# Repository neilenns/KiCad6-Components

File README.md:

# KiCad6 Custom Components

Custom components for use with KiCad 6.

## How to use

1. Clone the git repo.
2. Add a path in Kicad called `KICAD6_CUSTOM_COMPONENTS_DIR` that points to the locally cloned folder.
3. Add the `Custom_Symbols.kicad_sym` file as a custom symbol library.
4. Add the `Custom_Footprints.pretty` folder as a custom footprints library.

Here's an example of how the `Configure Paths` page should look;

Here's an example of how the `Symbols Libaries` page should look:

Here's an example of how the `Footprints Libraries` page should look:

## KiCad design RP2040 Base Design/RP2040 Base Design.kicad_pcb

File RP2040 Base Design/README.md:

# RP2040 Base PCB design

This KiCad template contains a base RP2040 schematic and PCB layout. To use this template go to _File_ > _New Project From Template..._,
switch to the _User Templates_ tab, then click the folder icon and navigate to this folder.

JLCPCB component numbers and footprints are included in the schematic as custom symbol properties.

**WARNING** While I've made a PCB using this design it was not done using this exact template. No boards have been ordered yet using this template so
if you use it and place an order while this message is still in place it is at your own risk.

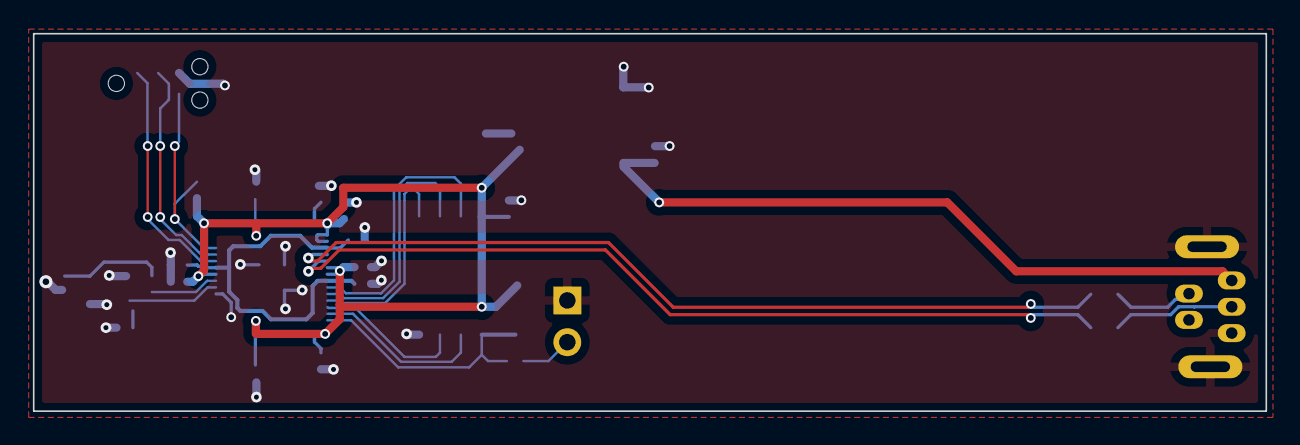
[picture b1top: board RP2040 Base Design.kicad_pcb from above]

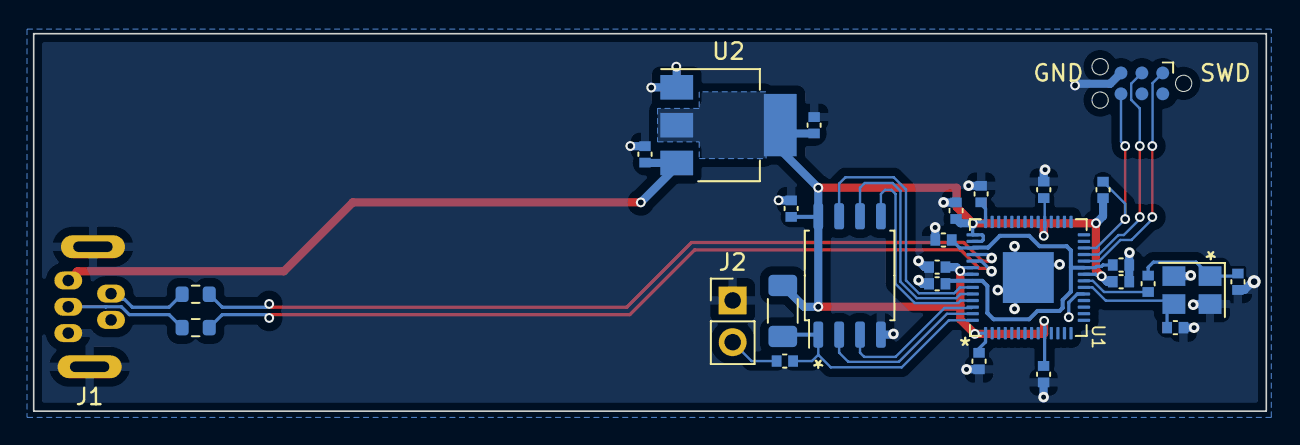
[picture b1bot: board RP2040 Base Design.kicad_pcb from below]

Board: 2 copper layers, 75.0 x 23.0 mm, 28 parts (28 on the bottom side), 21 nets.

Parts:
C1, C2, C3, C7, C10: 1uF; Perfect_0402
C4, C5: 10pF; Perfect_0402
C6, C8, C9, C11, C12, C13, C14, C15: 100nF; Perfect_0402
J1: USB_B_Micro; USB_B_Mini_Amphenol_UE25BE5510H
J2: Conn_01x02; PinHeader_1x02_P2.54mm_Vertical
J3: RP2040_SWD; Tag-Connect_TC2030-IDC-NL_2x03_P1.27mm_Vertical
R1, R2: 1k; Perfect_0402
R3, R4: 27; R_0603_1608Metric
R5: DNF; R_1206_3216Metric_Pad1.30x1.75mm_HandSolder
R6: 10k; Perfect_0402
U1: RP2040; QFN56P40_700X700X90L40X18T310N
U2: AMS1117-3.3; SOT-223-3_TabPin2
U3: W25Q128JVS; SOIC-8_5.23x5.23mm_P1.27mm
Y1: X322512MSB4SI; Crystal_SMD_3225-4Pin_3.2x2.5mm

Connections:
+1V1: C6.1, C7.1, C8.1, U1.23 (DVDD), U1.45 (VREG_VOUT), U1.50 (DVDD)
+3V3: C2.1, C3.1, C9.1, C10.1, C11.1, C12.1, C13.1, C14.1, C15.1, R5.1, R6.1, U1.1 (IOVDD), U1.10 (IOVDD), U1.22 (IOVDD), U1.33 (IOVDD), U1.42 (IOVDD), U1.43 (ADC_AVDD), U1.44 (VREG_IN), U1.48 (USB_VDD), U1.49 (IOVDD), U2.2 (VO), U3.8 (VCC)
+5V: C1.1, J1.1 (VBUS), U2.3 (VI)
/RP2040/QSPI_SCLK: U1.52 (QSPI_SCLK), U3.6 (CLK)
/RP2040/QSPI_SD0: U1.53 (QSPI_SD0), U3.5 (DI(IO0))
/RP2040/QSPI_SD1: U1.55 (QSPI_SD1), U3.2 (DO(IO1))
/RP2040/QSPI_SD2: U1.54 (QSPI_SD2), U3.3 (IO2)
/RP2040/QSPI_SD3: U1.51 (QSPI_SD3), U3.7 (IO3)
/RP2040/QSPI_SS: R1.1, R5.2, U1.56 (QSPI_SS), U3.1 (~CS)
/RP2040/SWCLK: J3.3, U1.25 (SWD)
/RP2040/SWD: J3.1, U1.24 (SWCLK)
/RP2040/USB_D+: J1.3 (D+), R3.1
/RP2040/USB_D-: J1.2 (D-), R4.1
/RP2040/USB_D_R+: R3.2, U1.47 (USB_DP)
/RP2040/USB_D_R-: R4.2, U1.46 (USB_DM)
/RP2040/XIN: C4.1, U1.20 (XIN), Y1.3
/RP2040/XOUT: C5.1, R2.2, Y1.1
/RP2040/XOUT_R: R2.1, U1.21 (XOUT)
/RP2040/~RST: J3.6, R6.2, U1.26 (RUN)
/RP2040/~USB_BOOT: J2.2, R1.2
GND: C1.2, C2.2, C3.2, C4.2, C5.2, C6.2, C7.2, C8.2, C9.2, C10.2, C11.2, C12.2, C13.2, C14.2, C15.2, J1.5 (GND), J1.6 (Shield), J2.1, J3.5, U1.19 (TESTEN), U1.57 (GND), U2.1 (GND), U3.4 (GND), Y1.2, Y1.4

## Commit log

2022-11-04 Add 6x6 push LED as a first test component.
2022-11-04 Add Perfect 0402 footprint
2022-11-04 Add USB_B_Mini_Amphenol_UE25BE5510H
2022-11-04 Update README.md
    Update how to use to reference the new file/folder names.
2022-11-04 Rename things
2022-11-09 Update README.md
    Correct the name of the path that has to get defined.
2022-11-09 Fix path to 3D model
2022-12-04 Add TCA8418
2022-12-04 Add TCA8418 datasheet
2022-12-05 Add RP2040 and DM13A
2022-12-05 Add mounting holes
2022-12-05 More footprints
2022-12-05 Create SW_PUSH_LED_SMD footprint
2022-12-29 Bunch of symbol updates!
2023-01-01 Add RP2040 base design
2023-01-01 Switch to KiCad template
2023-01-02 Move RP2040 to subsheet, fix up column names
2023-01-07 Add 10k pullup resistor to RUN pin for debugging Fixes #2
2023-01-07 Add default sizes
2023-01-07 Fix exposed pad for chip
2023-08-13 Fixes Fix cap values #6
